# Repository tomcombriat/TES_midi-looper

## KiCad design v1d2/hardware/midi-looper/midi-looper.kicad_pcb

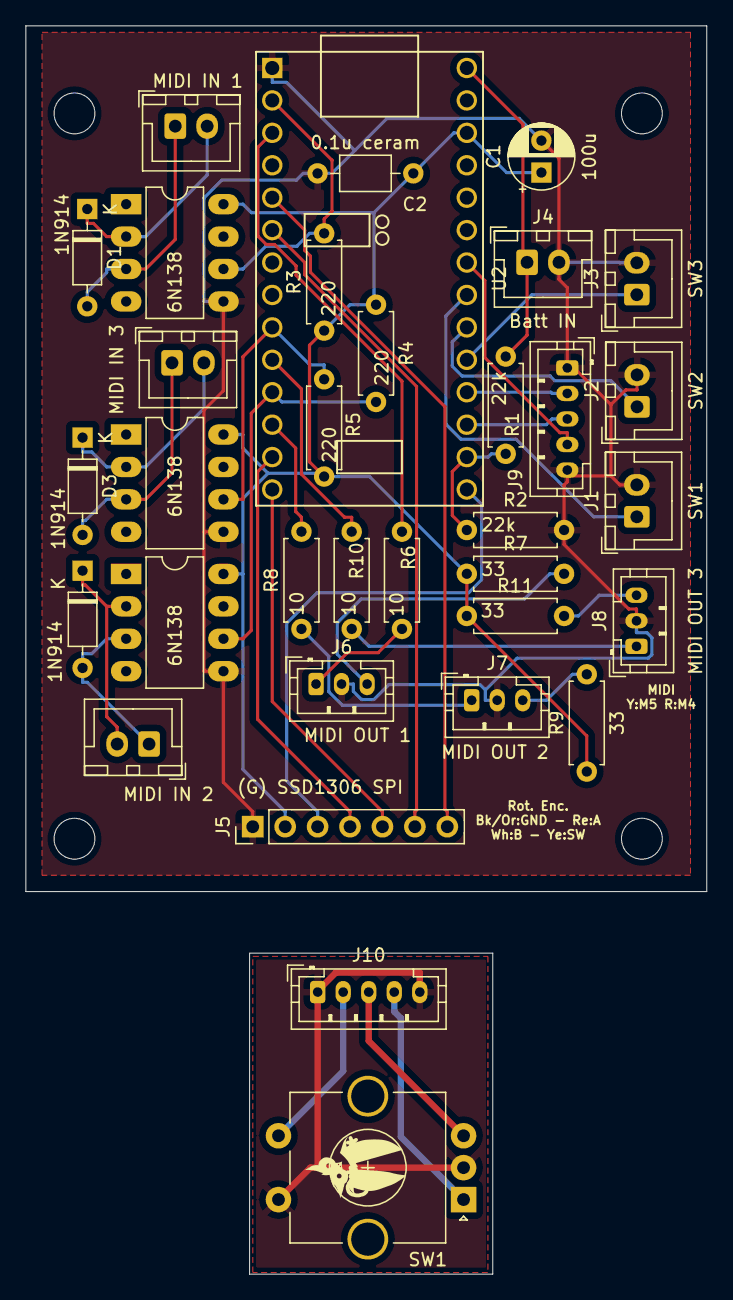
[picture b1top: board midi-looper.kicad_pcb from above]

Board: 2 copper layers, 53.3 x 67.8 mm, 38 parts (0 on the bottom side), 37 nets.

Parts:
C1: 100u; CP_Radial_D5.0mm_P2.50mm
C2: 0.1u ceram; C_Axial_L3.8mm_D2.6mm_P7.50mm_Horizontal
D1, D2, D3: 1N914; D_DO-35_SOD27_P7.62mm_Horizontal
H1, H2, H3, H4: MountingHole; MountingHole_3.2mm_M3
J1: SW1; JST_XH_B2B-XH-A_1x02_P2.50mm_Vertical
J2: SW2; JST_XH_B2B-XH-A_1x02_P2.50mm_Vertical
J3: SW3; JST_XH_B2B-XH-A_1x02_P2.50mm_Vertical
J4: Batt IN; JST_XH_B2B-XH-A_1x02_P2.50mm_Vertical
J5: (G) SSD1306 SPI; PinHeader_1x07_P2.54mm_Vertical
J6: MIDI OUT 1; JST_PH_B3B-PH-K_1x03_P2.00mm_Vertical
J7: MIDI OUT 2; JST_PH_B3B-PH-K_1x03_P2.00mm_Vertical
J8: MIDI OUT 3; JST_PH_B3B-PH-K_1x03_P2.00mm_Vertical
J9: Rot. Enc. Bk/Or:GND - Re:A - Wh:B - Ye:SW; JST_PH_B5B-PH-K_1x05_P2.00mm_Vertical
J10: Conn_01x05_Female; JST_PH_B5B-PH-K_1x05_P2.00mm_Vertical
J11: MIDI IN 1; JST_XH_B2B-XH-A_1x02_P2.50mm_Vertical
J12: MIDI IN 2; JST_XH_B2B-XH-A_1x02_P2.50mm_Vertical
J13: MIDI IN 3; JST_XH_B2B-XH-A_1x02_P2.50mm_Vertical
R1, R2: 22k; R_Axial_DIN0207_L6.3mm_D2.5mm_P7.62mm_Horizontal
R3, R4, R5: 220; R_Axial_DIN0207_L6.3mm_D2.5mm_P7.62mm_Horizontal
R6, R8, R10: 10; R_Axial_DIN0207_L6.3mm_D2.5mm_P7.62mm_Horizontal
R7, R9, R11: 33; R_Axial_DIN0207_L6.3mm_D2.5mm_P7.62mm_Horizontal
SW1: Rotary_Encoder_Switch; RotaryEncoder_Alps_EC11E-Switch_Vertical_H20mm_CircularMoun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
U1, U3, U4: 6N138; DIP-8_W7.62mm_LongPads
U2: Teensy3.2_breadboard_friendly; Teensy30_31_32_breadboard_friendly

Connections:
+3V3: C1.1, C2.1, J5.2, R3.1, R4.1, R5.1, R7.1, R9.1, R11.1, U1.8 (VCC), U2.31 (3.3V), U3.8 (VCC), U4.8 (VCC)
+5V: J4.1, R1.1, U2.33 (Vin)
/RX1: R3.2, U1.6 (VO2), U2.2 (0_RX1_Touch)
/RX2: R4.2, U2.11 (9_RX2_CS_PWM), U3.6 (VO2)
/RX3: R5.2, U2.9 (7_RX3_DOUT), U4.6 (VO2)
/TX1: R6.2, U2.3 (1_TX1_Touch)
/TX2: R8.2, U2.12 (10_TX2_CS_PWM)
/TX3: R10.2, U2.10 (8_TX3_DIN)
GND: C1.2, C2.2, J1.2, J2.2, J3.2, J4.2, J5.1, J6.2, J7.2, J8.2, J9.1, J9.5, R2.2, U1.5 (GND), U2.1 (GND), U3.5 (GND), U4.5 (GND)
unnamed: D1.1 (K), J11.2, U1.2 (C1)
unnamed: D1.2 (A), J11.1, U1.3 (C2)
unnamed: D2.1 (K), J12.2, U3.2 (C1)
unnamed: D2.2 (A), J12.1, U3.3 (C2)
unnamed: D3.1 (K), J13.2, U4.2 (C1)
unnamed: D3.2 (A), J13.1, U4.3 (C2)
unnamed: J1.1, U2.26 (19_A5_SCL0_Touch)
unnamed: J2.1, U2.25 (18_A4_SDA0_Touch)
unnamed: J3.1, U2.24 (17_A3_SDA0_Touch)
unnamed: J5.3, U2.20 (13_LED_SCK)
unnamed: J5.4, U2.13 (11_DOUT)
unnamed: J5.5, U2.14 (12_DIN)
unnamed: J5.6, U2.6 (4_RX_PWM)
unnamed: J5.7, U2.5 (3_TX_PWM)
unnamed: J6.1, R6.1
unnamed: J6.3, R7.2
unnamed: J7.1, R8.1
unnamed: J7.3, R9.2
unnamed: J8.1, R10.1
unnamed: J8.3, R11.2
unnamed: J9.2, U2.23 (16_A2_SCL0_Touch)
unnamed: J9.3, U2.22 (15_A1_CS_Touch)
unnamed: J9.4, U2.27 (20_A6_CS_PWM)
unnamed: J10.1, J10.5, SW1.C, SW1.S2
unnamed: J10.2, SW1.S1
unnamed: J10.3, SW1.B
unnamed: J10.4, SW1.A
unnamed: R1.2, R2.1, U2.21 (14_A0_SCK)

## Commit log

2021-12-10 Updated schematic
2021-12-10 Complete initial schematic
2021-12-10 Added net - assigned components
2021-12-27 Updated PCB and schem
2022-02-21 Started v1d1: smaller footprint as a goal
2022-02-21 Finalized compact version
2022-05-30 v1d2 for double sided pcb
